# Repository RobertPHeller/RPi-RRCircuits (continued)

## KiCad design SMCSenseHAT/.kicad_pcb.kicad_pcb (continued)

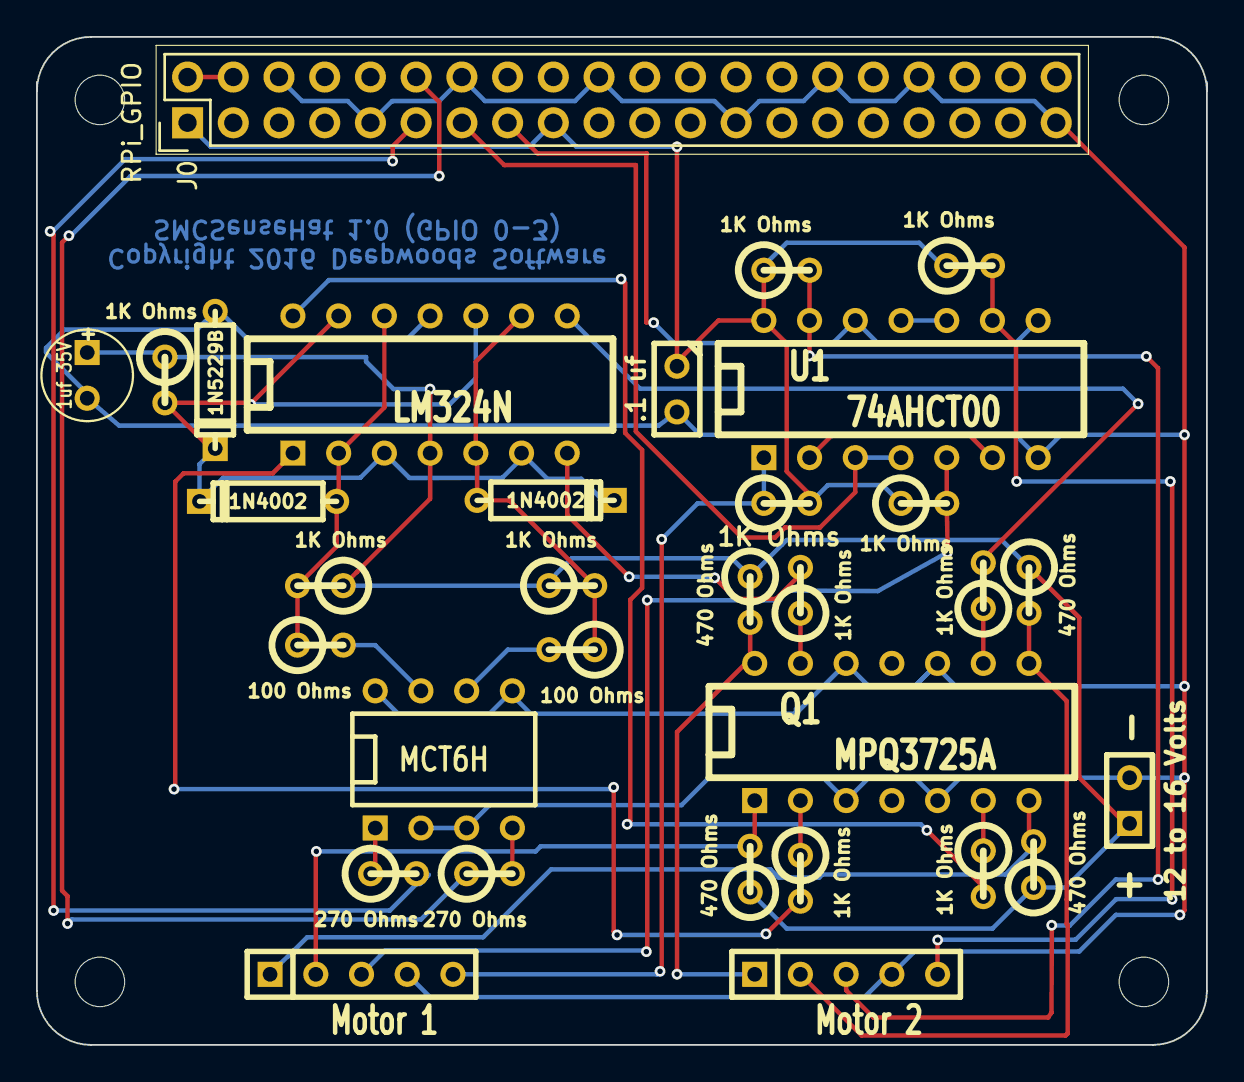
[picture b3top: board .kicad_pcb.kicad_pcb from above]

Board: 2 copper layers, 65.0 x 56.0 mm, 32 parts (1 on the bottom side), 33 nets.

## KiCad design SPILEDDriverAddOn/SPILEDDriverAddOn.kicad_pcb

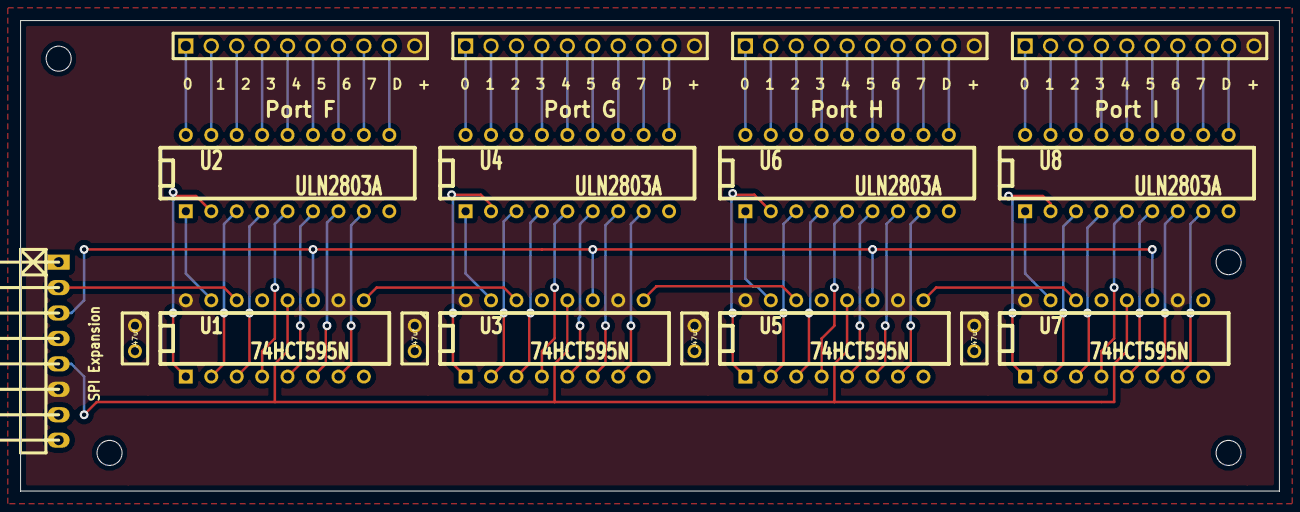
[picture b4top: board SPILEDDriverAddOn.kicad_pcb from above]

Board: 2 copper layers, 125.7 x 47.0 mm, 21 parts (0 on the bottom side), 76 nets.

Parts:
C1, C2, C3, C4: .47uf; C1
MH: MountingHole_2-5mm_RevA_Date21Jun2010
MH#2, MH#3, MH#4: MountingHole_2-5mm_RevA_Date21Jun2010
P1: SPI Expansion; pin_strip_8-90
P2, P3, P4, P5: 0 1 2 3 4 5 6 7 D +; ScrewTerm_2.54-10
U1, U3, U5, U7: 74HCT595N; DIP-16__300
U2, U4, U6, U8: ULN2803A; DIP-18__300

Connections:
+5V: C1.1, C2.1, C3.1, C4.1, P1.6, P2.10, P3.10, P4.10, P5.10, U1.10, U1.16, U3.10, U3.16, U5.10, U5.16, U7.10, U7.16
/Port F/Diode Up: P2.9, U2.10
/Port F/OLAT: P1.5, U1.12, U3.12, U5.12, U7.12
/Port F/SCK: P1.3, U1.11, U3.11, U5.11, U7.11
/Port F/Serial In: P1.2, U1.14
/Port G/Diode Up: P3.9, U4.10
/Port G/Serial In: U1.9, U3.14
/Port H/Diode Up: P4.9, U6.10
/Port H/Serial In: U3.9, U5.14
/Port I/Diode Up: P5.9, U8.10
/Port I/Serial In: U5.9, U7.14
GND: C1.2, C2.2, C3.2, C4.2, P1.8, U1.8, U1.13, U2.9, U3.8, U3.13, U4.9, U5.8, U5.13, U6.9, U7.8, U7.13, U8.9
unnamed: P2.4, U2.15
unnamed: P2.3, U2.16
unnamed: P2.2, U2.17
unnamed: P2.1, U2.18
unnamed: P2.5, U2.14
unnamed: P2.6, U2.13
unnamed: P2.7, U2.12
unnamed: U1.6, U2.7
unnamed: U1.7, U2.8
unnamed: P2.8, U2.11
unnamed: U1.3, U2.4
unnamed: U1.5, U2.6
unnamed: U1.1, U2.2
unnamed: U1.2, U2.3
unnamed: U1.4, U2.5
unnamed: U1.15, U2.1
unnamed: P3.2, U4.17
unnamed: P3.3, U4.16
unnamed: P3.4, U4.15
unnamed: P3.5, U4.14
unnamed: P3.6, U4.13
unnamed: U3.6, U4.7
unnamed: U3.7, U4.8
unnamed: P3.1, U4.18
unnamed: P3.7, U4.12
unnamed: P3.8, U4.11
unnamed: U3.3, U4.4
unnamed: U3.5, U4.6
unnamed: U3.1, U4.2
unnamed: U3.2, U4.3
unnamed: U3.4, U4.5
unnamed: U3.15, U4.1
unnamed: P4.1, U6.18
unnamed: P4.2, U6.17
unnamed: P4.3, U6.16
unnamed: P4.4, U6.15
unnamed: P4.5, U6.14
unnamed: P4.6, U6.13
unnamed: P4.7, U6.12
unnamed: U5.6, U6.7
unnamed: U5.7, U6.8
unnamed: P4.8, U6.11
unnamed: U5.3, U6.4
unnamed: U5.5, U6.6
unnamed: U5.1, U6.2
unnamed: U5.2, U6.3
unnamed: U5.4, U6.5
unnamed: U5.15, U6.1
unnamed: P5.1, U8.18
unnamed: P5.2, U8.17
unnamed: P5.3, U8.16
unnamed: P5.4, U8.15
unnamed: P5.5, U8.14
unnamed: P5.6, U8.13
unnamed: P5.7, U8.12
unnamed: U7.6, U8.7
unnamed: U7.7, U8.8
unnamed: P5.8, U8.11
unnamed: U7.3, U8.4
unnamed: U7.5, U8.6
unnamed: U7.1, U8.2
unnamed: U7.2, U8.3
unnamed: U7.4, U8.5
unnamed: U7.15, U8.1

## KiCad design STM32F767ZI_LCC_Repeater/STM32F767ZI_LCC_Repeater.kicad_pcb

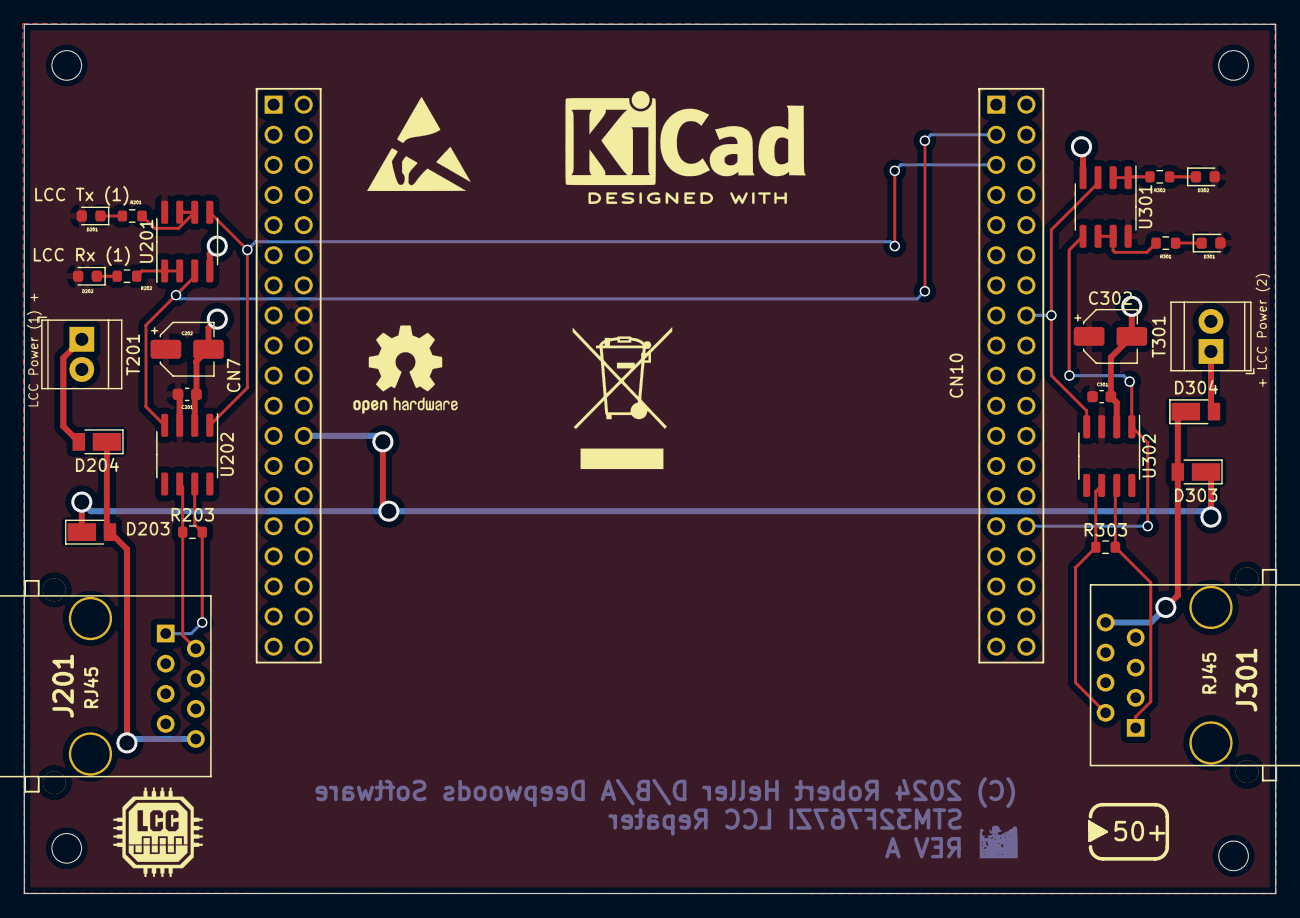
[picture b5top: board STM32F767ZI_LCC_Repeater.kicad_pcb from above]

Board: 2 copper layers, 105.6 x 73.3 mm, 32 parts (0 on the bottom side), 23 nets.

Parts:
C201, C301: .1 uf; C_0603_1608Metric
C202, C302: 15 uf 15V; CP_Elec_4x5.8
CN7, CN10: ST_MORPHO; ST_Morpho
D201: LCC Tx (1); LED_0603_1608Metric
D202: LCC Rx (1); LED_0603_1608Metric
D203, D204, D303, D304: SB240; D_PowerDI-123
D301: LCC Tx (2); LED_0603_1608Metric
D302: LCC Rx (2); LED_0603_1608Metric
J201, J301: RJ45; RJ45_8N-S
MH: MountingHole_2-5mm_RevA_Date21Jun2010
MH#2, MH#3, MH#4: MountingHole_2-5mm_RevA_Date21Jun2010
R201, R202, R301, R302: 160 Ohms; R_0603_1608Metric
R203, R303: 120; R_0603_1608Metric
T201: LCC Power (1) +; TerminalBlock_TE_282834-2_1x02_P2.54mm_Horizontal
T301: + LCC Power (2); TerminalBlock_TE_282834-2_1x02_P2.54mm_Horizontal
U201, U301: LM358; SOIC-8_3.9x4.9mm_P1.27mm
U202, U302: TCAN332DR; SOIC-8_3.9x4.9mm_P1.27mm

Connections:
+3.3V: C201.1, C202.1, C301.1, C302.1, CN7.16, D201.2 (A), D202.2 (A), D301.2 (A), D302.2 (A), U201.8 (V+), U202.3 (Vcc), U301.8 (V+), U302.3 (Vcc)
/PB8-CAN1_RX: CN10.3, U201.3 (+), U202.4 (R)
/PB9-CAN1_TX: CN10.5, U201.5 (+), U202.1 (D)
/PB12-CAN2_RX: CN10.16, U301.3 (+), U302.4 (R)
/PB13-CAN2_TX: CN10.30, U301.5 (+), U302.1 (D)
/VIN: CN7.24, D203.1 (K), D303.1 (K)
GND: C201.2, C202.2, C301.2, C302.2, CN7.8, CN7.19, CN7.20, CN7.22, CN10.9, CN10.20, J201.3, J201.6, J201.7, J301.3, J301.6, J301.7, T201.2, T301.2, U201.4 (V-), U202.2 (GND), U301.4 (V-), U302.2 (GND)
unnamed: D201.1 (K), R201.1
unnamed: D202.1 (K), R202.1
unnamed: D203.2 (A), D204.1 (K), J201.8
unnamed: D204.2 (A), T201.1
unnamed: D301.1 (K), R301.1
unnamed: D302.1 (K), R302.1
unnamed: D303.2 (A), D304.1 (K), J301.8
unnamed: D304.2 (A), T301.1
unnamed: J201.1, R203.2, U202.7 (CANH)
unnamed: J201.2, R203.1, U202.6 (CANL)
unnamed: J301.1, R303.2, U302.7 (CANH)
unnamed: J301.2, R303.1, U302.6 (CANL)
unnamed: R201.2, U201.6 (-), U201.7
unnamed: R202.2, U201.1, U201.2 (-)
unnamed: R301.2, U301.6 (-), U301.7
unnamed: R302.2, U301.1, U301.2 (-)
